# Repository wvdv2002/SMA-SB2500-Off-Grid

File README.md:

# SMA-SB2500-Off-Grid
The grid tie solar inverter SMA Sunny Boy SB2500 is a beautifully designed transformer isolated grid tie inverter. It is probably possible to convert it to an off grid batter inverter by reprogramming or redesigning the logic  board

Checkout my [hackaday.io](https://hackaday.io/project/183357-grid-tie-inverter-sma-sunny-boy-sb2500-openlogic) page for pictures of the inside of the inverter and a project log.

The block diagram from the SB2500 manual.

The inverter has an H-bridge with 4 IGBTs (SKW30NF60) driven by IR2113S mosfet drivers. These drive an 2mH inductor + 4.7uF capacitor step down converter and then a isolation transformer 153V primary/230V secondary 9.6A. On the grid side are three safety relais, EMC filtering and a measurement transformer for the logic board the measure the grid voltages.
All the logic is powered from the DC side, several voltages are generated using a switching power converter which generates all the drive voltages for the IGBT drivers and the logi board.
The logic board contains an SAFC808 microcontroller, probably with an interchangable AT70C020, 2 MBit memory chip, for grid monitoring and sequencing. A DSP56F803 from Freescale provides the switching waveforms. 

The layout is drawn in Kicad. 

Exported kicad images (probably not up to date) are in the images folder. 

The src folder can contain the Freescale DSP code.

The datasheets folder contains datasheets of most of the electronic parts in the inverter.

# Already known
* Switching frequency 16khz
* 250 - 600VDC max input voltage range
* 2200W nominal power
* It is probably challenging to reuse the logic board, as one of the microcontrollers is OTP, maybe it can be bridged and only the DSP used. But then you need a [Freescale USB TAP](https://www.nxp.com/docs/en/user-guide/CWH-UTP-UG.pdf) JTAG programmer to program the DSP. The development environment is not easy to download, but it looks easy to use. 
* The [DEFCON 18 badge](https://media.defcon.org/DEF%20CON%2018/DEF%20CON%2018%20badge/) has used the same development environment and might be a good place to download the development environment and some general guide.

# Already done
* Basic pinout of the logic board connection in Kicad
* Basic layout of the power board important parts in Kicad
* Design new logic board 
* Check if pinout is correct by measuring the voltages on the logic board connector 
* Check all voltage ranges of the voltage measurements on the logic board connector
* Written basic control software
* Light a lightbulb using AC voltage of 100vac at the output of the inverter.

# TODO
* Try to reprogram logic board

# Interesting links
* [Arduino based grid tie inverter repo](https://github.com/MartinStokroos/openMicroInverter)
* [Pic based grid tie inverter repo](https://github.com/rajeshfarswan/UDQ-GRID-1P)
* [STM based grid tie inverter repo](https://github.com/fotherja/Grid_Tie_Inverter)
* [STM based grid tie inverter 2 repo](https://github.com/fotherja/Grid_Tie_Inverter_2)
* [TIVA-C based grid tie inverter](https://github.com/srpoyrek/NIVAS)

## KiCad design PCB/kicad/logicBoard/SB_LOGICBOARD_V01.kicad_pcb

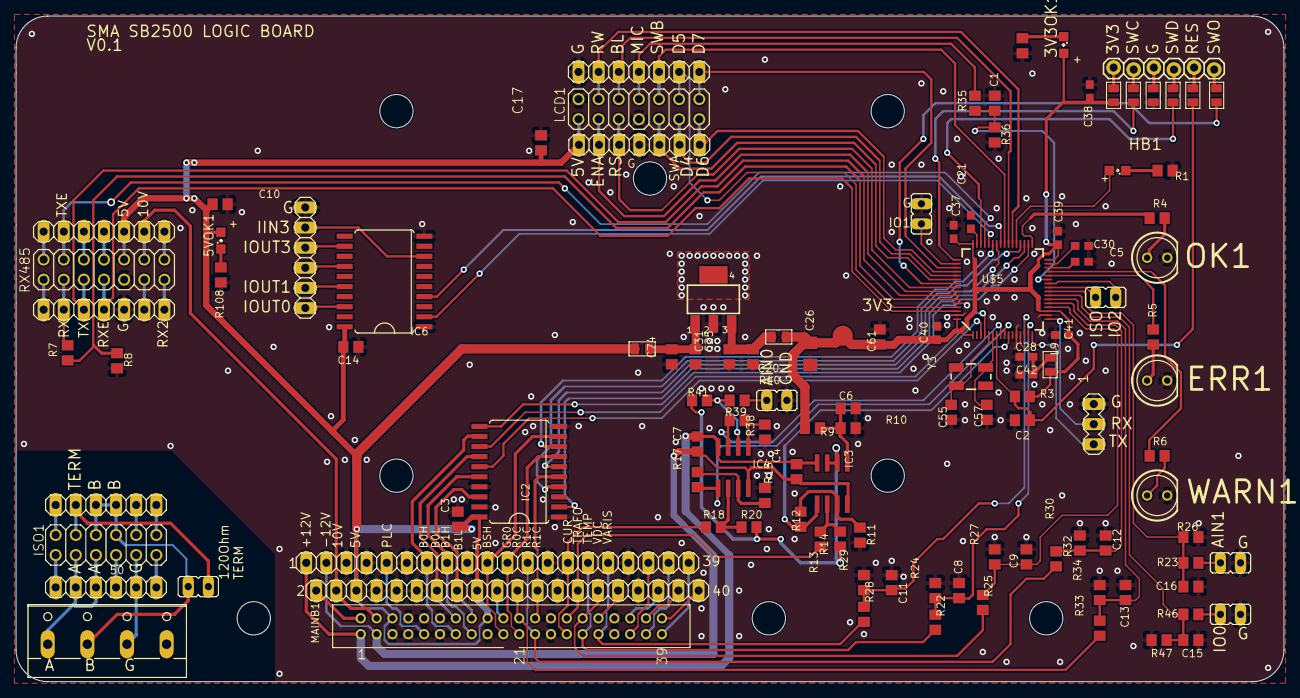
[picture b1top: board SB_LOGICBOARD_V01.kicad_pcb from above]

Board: 2 copper layers, 160.0 x 84.0 mm, 119 parts (0 on the bottom side), 132 nets.

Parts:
3V3: NC; B2,54
3V3OK1, 5VOK1: OSR50805C1E; SML0805
AIN0: JP1E; JP1
C1, C4, C6, C7, C8, C9, C11, C12, C13, C15, C16: 100n/35v; C0805
C2, C3, C10, C14, C17, C20, C25, C31, C61, C74: 100n; C0805
C5: NC; C0603
C21, C28, C30, C37, C38, C39, C40, C41, C42: 2.2uf/6.3v/x7r; C0603
C26: 1206DD106KAT2A; C1206
C55, C57: 22pf; C0805
ERR1: LED5MM
HB1: OSR50805C1E; SML0805
IC1: MCP1826S-3302ED; SOT223
IC2, IC6: 74HCT244DW OR 74VHCT541A; SO20W
IC3, IC4: LM358D; SO08
ISO1: PINHD-2X6; 2X06
J1: ZL201-06G; 1X06_LOCK
JP5, JP6: PINHD-1X20; 1X20
JP7, JP8, JP11, JP12: PINHD-1X7; 1X07
JP9, JP10, JP17: PINHD-1X6; 1X06
JP13, JP15, JP16, JP18, JP19: JP1E; JP1
L1, L2, L3, L6, L7, L8, L9, L26, L27: LCBB-601; L0805
LCD1: PINHD-2X7; 2X07
MAINB1: PINHD-2X20_2MM; 2X20_2MM
OK1: LED5MM
R1, R4, R5, R6: 330; R0805
R3, R12, R14, R17, R20, R39, R41: 10k; R0805
R7, R22, R23, R25, R28, R30, R33, R35, R46: 10K; R0805
R8, R24, R26, R27, R29, R32, R34, R36, R47: 22K; R0805
R9, R10: 22k; R0805
R11, R13: 33k; R0805
R15, R18, R38, R40: 39k; R0805
R108, R109: 2k2/1%; R0805
RX485: PINHD-2X7; 2X07
SV1: MA03-1
U$1: SB_LOGIC_PCB; SB-PCB
U$5: STM32F405RG; TQFP64
WARN1: LED5MM
X1: W237-4
Y3: 8.00M-CFPX104; CRYSTAL-SMD-5X3

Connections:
+3V3: 3V3.TP, 3V3OK1.A, C26.2, C37.1, C38.1, C39.1, C40.1, C41.1, C61.2, L8.1, L9.2, L27.2, R3.2, R9.2, U$5.1, U$5.19, U$5.32, U$5.48, U$5.64
+5V: 5VOK1.A, C3.1, C10.2, C14.1, C17.2, IC2.20, IC6.20, JP6.3, JP6.9, JP8.5, JP11.1, L26.1, LCD1.1, MAINB1.6, MAINB1.18, RX485.10
+12V: C4.1, C7.1, IC3.8, IC4.8, JP5.1, MAINB1.1
-12V: C4.2, C7.2, IC3.4, IC4.4, JP5.2, MAINB1.3
/Microcontroller/IO_IN1: JP19.1, U$5.50
/Microcontroller/IO_IN2: JP18.1, U$5.26
/Microcontroller/ISOLATION_SENSE: JP18.2, U$5.25
/Microcontroller/USART2_RX: SV1.2, U$5.17
/Microcontroller/USART2_TX: SV1.3, U$5.16
/SB_HEADERS/50OHMTOGND: ISO1.7, JP10.4
/SB_HEADERS/120OHMTOA: ISO1.4, JP9.2, JP13.2
/SB_HEADERS/AC_MODEM: JP5.5, MAINB1.9
/SB_HEADERS/ADC_IN0_5V: AIN0.2, R40.1
/SB_HEADERS/ADC_IN1_5V: JP15.2, R23.2
/SB_HEADERS/ADC_UNKNOWN: JP6.16, MAINB1.32
/SB_HEADERS/BRIDGE0_HIN_5V: IC2.12, JP5.7, MAINB1.13
/SB_HEADERS/BRIDGE0_LIN_5V: IC2.14, JP6.7, MAINB1.14
/SB_HEADERS/BRIDGE1_HIN_5V: IC2.16, JP5.8, MAINB1.15
/SB_HEADERS/BRIDGE1_LIN_5V: IC2.18, JP6.8, MAINB1.16
/SB_HEADERS/BRIDGES_SHUTDOWN_5V: IC2.9, JP5.10, MAINB1.19
/SB_HEADERS/CURSENS_5V: JP5.14, MAINB1.27, R18.1
/SB_HEADERS/GRIDRELAY_0_5V: IC2.7, JP5.11, MAINB1.21
/SB_HEADERS/GRIDRELAY_1_5V: IC2.5, JP6.12, MAINB1.24
/SB_HEADERS/IO_IN0_5V: JP16.2, R46.2
/SB_HEADERS/IO_OUT0_5V: IC6.18, JP17.6
/SB_HEADERS/IO_OUT1_5V: IC6.16, JP17.5
/SB_HEADERS/IO_OUT2_5V: IC6.14, JP17.4
/SB_HEADERS/IO_OUT3: IC6.8, JP17.2
/SB_HEADERS/IO_OUT3_5V: IC6.12, JP17.3
/SB_HEADERS/LCD_MIC_5V: JP12.4, LCD1.8, R35.2
/SB_HEADERS/N$25: ISO1.2, JP9.1
/SB_HEADERS/N$29: ISO1.10, JP9.5
/SB_HEADERS/N$30: ISO1.12, JP9.6
/SB_HEADERS/N$31: ISO1.1, JP10.1
/SB_HEADERS/N$42: ISO1.11, JP10.6
/SB_HEADERS/N$53: JP6.10, MAINB1.20
/SB_HEADERS/N$62: JP6.19, MAINB1.38
/SB_HEADERS/N$63: JP6.20, MAINB1.40
/SB_HEADERS/N$86: JP5.18, MAINB1.35
/SB_HEADERS/N$87: JP5.19, MAINB1.37
/SB_HEADERS/N$88: JP5.20, MAINB1.39
/SB_HEADERS/NC1: JP8.3, RX485.6
/SB_HEADERS/NC2: JP8.4, RX485.8
/SB_HEADERS/NC3: JP7.6, RX485.11
/SB_HEADERS/NC4: JP8.7, RX485.14
/SB_HEADERS/NC5: JP8.1, RX485.2
/SB_HEADERS/NC6: JP7.1, RX485.1
/SB_HEADERS/RELAY0_CHECK_5V: JP6.11, MAINB1.22, R33.2
/SB_HEADERS/RELAY1_CHECK_5V: JP5.12, MAINB1.23, R30.2
/SB_HEADERS/RS485_A: ISO1.3, ISO1.5, JP10.2, JP10.3, X1.1
/SB_HEADERS/RS485_B: ISO1.6, ISO1.8, JP9.3, JP9.4, JP13.1, X1.2
/SB_HEADERS/RS485_GND: ISO1.9, JP10.5, X1.3
/SB_HEADERS/RS485_RX_5V: JP7.2, R7.2, RX485.3
/SB_HEADERS/RX2: JP7.7, RX485.13
/SB_HEADERS/SOMESIGNAL: JP6.18, MAINB1.36
/SB_HEADERS/TEMPHEAT_5V: JP5.15, MAINB1.29, R22.2
/SB_HEADERS/TRAFO_5V: JP6.14, MAINB1.28, R13.1
/SB_HEADERS/VARISTOR_SENSE_5V: JP5.16, MAINB1.31, R28.2
/SB_HEADERS/VDCBUS_5V: JP6.15, MAINB1.30, R25.2
/SB_HEADERS/VSUP3: JP6.2, JP8.6, MAINB1.4, RX485.12
ADC_IN0: IC4.7, R39.2, U$5.8
ADC_IN1: C16.1, R23.1, R26.2, U$5.24
BRIDGE0_HIN: IC2.6, U$5.42
BRIDGE0_LIN: IC2.2, U$5.35
BRIDGE1_HIN: IC2.8, U$5.43
BRIDGE1_LIN: IC2.4, U$5.36
BRIDGES_SHUTDOWN: IC2.11, U$5.34
CURSENS: IC4.1, R17.2, U$5.9
GND: AIN0.1, C1.2, C2.1, C3.2, C5.2, C6.2, C8.2, C9.2, C10.1, C11.2, C12.2, C13.2, C14.2, C15.2, C16.2, C17.1, C20.1, C21.1, C25.1, C26.1, C28.2, C30.2, C31.1, C37.2, C38.2, C39.2, C40.2, C41.2, C42.2, C55.2, C57.2, C61.1, C74.2, ERR1.K, IC1.2, IC2.1, IC2.10, IC2.17, IC2.19, IC6.1, IC6.10, JP5.3, JP5.4, JP5.6, JP5.9, JP5.13, JP5.17, JP6.4, JP6.5, JP6.6, JP6.13, JP6.17, JP7.5, JP11.4, JP12.1, JP15.1, JP16.1, JP17.1, JP19.2, L6.1, LCD1.2, LCD1.7, MAINB1.5, MAINB1.7, MAINB1.8, MAINB1.10, MAINB1.11, MAINB1.12, MAINB1.17, MAINB1.25, MAINB1.26, MAINB1.33, MAINB1.34, OK1.K, R1.1, R8.1, R10.1, R11.1, R15.1, R24.1, R26.1, R27.1, R29.1, R32.1, R34.1, R36.1, R38.1, R47.1, R108.1, R109.1, RX485.9, SV1.1, U$5.12, U$5.18, U$5.60, U$5.63, WARN1.K
GRIDRELAY_0: IC2.13, U$5.4
GRIDRELAY_1: IC2.15, U$5.3
HEARTBEAT_LED: HB1.A, U$5.37
IO_IN0: C15.1, R46.1, R47.2, U$5.23
IO_OUT0: IC6.2, U$5.44
IO_OUT1: IC6.4, U$5.41
LCD_BACKL: JP12.3, LCD1.6, U$5.39
LCD_D4: JP11.6, LCD1.11, U$5.53
LCD_D5: JP12.6, LCD1.12, U$5.61
LCD_D6: JP11.7, LCD1.13, U$5.52
LCD_D7: JP12.7, LCD1.14, U$5.51
LCD_ENA: JP11.2, LCD1.3, U$5.57
LCD_MIC: C1.1, R35.1, R36.2, U$5.27
LCD_RS: JP11.3, LCD1.5, U$5.56
LCD_RW: JP12.2, LCD1.4, U$5.38
LCD_SWA: JP11.5, LCD1.9, U$5.54
LCD_SWB: JP12.5, LCD1.10, U$5.40
LED_GREEN: R4.1, U$5.33
LED_RED: R5.1, U$5.28
LED_YELLOW: R6.1, U$5.29
unnamed: 3V3OK1.C, R109.2
unnamed: 5VOK1.C, R108.2
unnamed: C5.1, U$5.30
unnamed: C6.1, IC3.5, R9.1, R10.2
unnamed: C20.2, C25.2, IC1.3, L27.1
unnamed: C21.2, U$5.47
unnamed: C28.1, C42.1, L9.1, U$5.13
unnamed: C30.1, U$5.31
unnamed: C31.2, C74.1, IC1.1, L26.2
unnamed: C55.1, U$5.5, Y3.1
unnamed: C57.1, U$5.6, Y3.3
unnamed: ERR1.A, R5.2
unnamed: HB1.C, R1.2
unnamed: IC3.2, R13.2, R14.1
unnamed: IC3.3, R11.2, R12.1
unnamed: IC4.2, R18.2, R20.1
unnamed: IC4.3, R15.2, R17.1
unnamed: IC4.5, R38.2, R39.1
unnamed: IC4.6, R40.2, R41.1
unnamed: J1.1, L8.2
unnamed: J1.2, L7.2
unnamed: J1.3, L6.2
unnamed: J1.4, L3.2
unnamed: J1.5, L2.2
unnamed: J1.6, L1.2
unnamed: JP6.1, MAINB1.2
unnamed: OK1.A, R4.2
unnamed: R6.2, WARN1.A
RELAY0_CHECK: C13.1, R33.1, R34.2, U$5.22
RELAY1_CHECK: C12.1, R30.1, R32.2, U$5.21
RESET: C2.2, L2.1, R3.1, U$5.7
RS485_RX: R7.1, R8.2, U$5.59
RS485_RXENA: JP7.4, RX485.7, U$5.62
RS485_TX: JP7.3, RX485.5, U$5.58
RS485_TXENA: JP8.2, RX485.4, U$5.45
SWCLK: L7.1, U$5.49
SWDIO: L3.1, U$5.46
SWO: L1.1, U$5.55
TEMPHEAT: C8.1, R22.1, R24.2, U$5.15
TRAFO: IC3.1, R12.2, U$5.10
VARISTOR_SENSE: C11.1, R28.1, R29.2, U$5.14
VCC/2: IC3.6, IC3.7, R14.2, R20.2, R41.2
VDCBUS: C9.1, R25.1, R27.2, U$5.20

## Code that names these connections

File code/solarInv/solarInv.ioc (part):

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Mcu.Name=STM32F405RGTx
Mcu.Package=LQFP64
Mcu.UserName=STM32F405RGTx
PA0-WKUP.Signal=ADCx_IN0
PA1.GPIOParameters=GPIO_Label
PA1.GPIO_Label=TEMPHEAT
PA1.Signal=ADCx_IN1
PA10.GPIOParameters=GPIO_Speed,GPIO_Label
PA10.GPIO_Label=BRIDGE1_HIN
PA10.GPIO_Speed=GPIO_SPEED_FREQ_HIGH
PA10.Signal=S_TIM1_CH3
PA11.GPIOParameters=GPIO_Label
PA11.GPIO_Label=IO_OUT0
PA11.Signal=GPIO_Output
PA12.GPIOParameters=GPIO_Label
PA12.GPIO_Label=RS485_TXENA
PA12.Signal=GPIO_Output
PA13.Mode=Trace_Asynchronous_SW
PA13.Signal=SYS_JTMS-SWDIO
PA14.Mode=Trace_Asynchronous_SW
PA14.Signal=SYS_JTCK-SWCLK
PA15.GPIOParameters=GPIO_PuPd,GPIO_Label
PA15.GPIO_Label=IO_IN1
PA15.GPIO_PuPd=GPIO_NOPULL
PA15.Signal=GPIO_Input
PA2.GPIOParameters=GPIO_Speed,GPIO_Label
PA2.GPIO_Label=USART2_TX
PA2.GPIO_Speed=GPIO_SPEED_FREQ_HIGH
PA2.Mode=Asynchronous
PA2.Signal=USART2_TX
PA3.GPIOParameters=GPIO_Speed,GPIO_Label
PA3.GPIO_Label=USART2_RX
PA3.GPIO_Speed=GPIO_SPEED_FREQ_HIGH
PA3.Mode=Asynchronous
PA3.Signal=USART2_RX
PA4.GPIOParameters=GPIO_Label
PA4.GPIO_Label=VDCBUS
PA4.Signal=ADCx_IN4
PA5.GPIOParameters=GPIO_Label
PA5.GPIO_Label=RELAY_CHECK1
PA5.Signal=ADCx_IN5
PA6.GPIOParameters=GPIO_Label
PA6.GPIO_Label=RELAY_CHECK0
PA6.Signal=ADCx_IN6
PA7.GPIOParameters=GPIO_Label
PA7.GPIO_Label=IO_IN0
PA7.Signal=ADCx_IN7
PA8.GPIOParameters=GPIO_Label
PA8.GPIO_Label=IO_OUT1
PA8.Signal=GPIO_Output
PA9.GPIOParameters=GPIO_Speed,GPIO_Label
PA9.GPIO_Label=BRIDGE0_HIN
PA9.GPIO_Speed=GPIO_SPEED_FREQ_HIGH
PA9.Signal=S_TIM1_CH2
PB0.GPIOParameters=GPIO_Label
PB0.GPIO_Label=IO_IN2
PB0.Signal=ADCx_IN8
PB1.GPIOParameters=GPIO_Label
PB1.GPIO_Label=LCD_MIC
PB1.Signal=ADCx_IN9
PB10.GPIOParameters=GPIO_Label
PB10.GPIO_Label=LED_YELLOW
PB10.Signal=GPIO_Output
PB11.GPIOParameters=GPIO_PuPd,GPIO_Label,GPIO_Mode
PB11.GPIO_Label=DONOTUSECOMPATIBILITY
PB11.GPIO_Mode=GPIO_MODE_INPUT
PB11.GPIO_PuPd=GPIO_NOPULL
PB11.Signal=GPIO_Input
PB12.GPIOParameters=GPIO_Label
PB12.GPIO_Label=LED_GREEN
PB12.Signal=GPIO_Output
PB13.GPIOParameters=GPIO_Speed,PinState,GPIO_Label
PB13.GPIO_Label=BRIDGES_SHUTDOWN
PB13.GPIO_Speed=GPIO_SPEED_FREQ_MEDIUM
PB13.PinState=GPIO_PIN_SET
PB13.Signal=GPIO_Output
PB14.GPIOParameters=GPIO_ModeDefaultPP,GPIO_Speed,GPIO_PuPd,GPIO_Label
PB14.GPIO_Label=BRIDGE0_LIN
PB14.GPIO_ModeDefaultPP=GPIO_MODE_AF_PP
PB14.GPIO_PuPd=GPIO_NOPULL
PB14.GPIO_Speed=GPIO_SPEED_FREQ_HIGH
PB14.Mode=PWM Generation2 CH2 CH2N
PB14.Signal=TIM1_CH2N
PB15.GPIOParameters=GPIO_ModeDefaultPP,GPIO_Speed,GPIO_PuPd,GPIO_Label
PB15.GPIO_Label=BRIDGE1_LIN
PB15.GPIO_ModeDefaultPP=GPIO_MODE_AF_PP
PB15.GPIO_PuPd=GPIO_NOPULL
PB15.GPIO_Speed=GPIO_SPEED_FREQ_HIGH
PB15.Mode=PWM Generation3 CH3 CH3N
PB15.Signal=TIM1_CH3N
PB2.GPIOParameters=GPIO_Label
PB2.GPIO_Label=LED_RED
PB2.Signal=GPIO_Output
PB3.Mode=Trace_Asynchronous_SW
PB3.Signal=SYS_JTDO-SWO
PB4.GPIOParameters=GPIO_Label
PB4.GPIO_Label=LCD_RS
PB4.Signal=GPIO_Output
PB5.GPIOParameters=GPIO_Speed,PinState,GPIO_PuPd,GPIO_Label,GPIO_ModeDefaultOutputPP
PB5.GPIO_Label=LCD_ENA
PB5.GPIO_ModeDefaultOutputPP=GPIO_MODE_OUTPUT_PP
PB5.GPIO_PuPd=GPIO_NOPULL
PB5.GPIO_Speed=GPIO_SPEED_FREQ_LOW
PB5.PinState=GPIO_PIN_RESET
PB5.Signal=GPIO_Output
PB6.GPIOParameters=GPIO_Speed,GPIO_Label
PB6.GPIO_Label=RS485_TX
PB6.GPIO_Speed=GPIO_SPEED_FREQ_HIGH
PB6.Mode=Asynchronous
PB6.Signal=USART1_TX
PB7.GPIOParameters=GPIO_Speed,GPIO_Label
PB7.GPIO_Label=RS485_RX
PB7.GPIO_Speed=GPIO_SPEED_FREQ_HIGH
PB7.Mode=Asynchronous
PB7.Signal=USART1_RX
PB8.GPIOParameters=GPIO_Label
PB8.GPIO_Label=LCD_D5
PB8.Signal=GPIO_Output
PB9.GPIOParameters=GPIO_Label
PB9.GPIO_Label=RS485_RXENA
PB9.Signal=GPIO_Output
PC0.GPIOParameters=GPIO_Label
PC0.GPIO_Label=ADC_IN0
PC0.Signal=ADCx_IN10
PC1.GPIOParameters=GPIO_PuPd,GPIO_Label,GPIO_Mode
PC1.GPIO_Label=CURSENS
PC1.GPIO_Mode=GPIO_MODE_ANALOG
PC1.GPIO_PuPd=GPIO_NOPULL
PC1.Signal=ADCx_IN11
PC10.GPIOParameters=GPIO_Label
PC10.GPIO_Label=LCD_D7
PC10.Signal=GPIO_Output
PC11.GPIOParameters=GPIO_Label
PC11.GPIO_Label=LCD_D6
PC11.Signal=GPIO_Output
PC12.GPIOParameters=GPIO_Label
PC12.GPIO_Label=LCD_D4
PC12.Signal=GPIO_Output
PC14-OSC32_IN.GPIOParameters=GPIO_Label
PC14-OSC32_IN.GPIO_Label=GRIDRELAY_1
PC14-OSC32_IN.Signal=GPIO_Output
PC15-OSC32_OUT.GPIOParameters=GPIO_Label
PC15-OSC32_OUT.GPIO_Label=GRIDRELAY_0
PC15-OSC32_OUT.Signal=GPIO_Output
PC2.GPIOParameters=GPIO_PuPd,GPIO_Label,GPIO_Mode
PC2.GPIO_Label=TRAFO
PC2.GPIO_Mode=GPIO_MODE_ANALOG
PC2.GPIO_PuPd=GPIO_NOPULL
PC2.Signal=ADCx_IN12
PC4.GPIOParameters=GPIO_Label
PC4.GPIO_Label=ADC_IN1
PC4.Signal=ADCx_IN14
PC5.GPIOParameters=GPIO_Label
PC5.GPIO_Label=ISOLATION_SENSE
PC5.Signal=ADCx_IN15
PC6.GPIOParameters=GPIO_Label
PC6.GPIO_Label=LED_HEARTBEAT
PC6.Signal=GPIO_Output
PC7.GPIOParameters=GPIO_Label
PC7.GPIO_Label=LCD_RW
PC7.Signal=GPIO_Output
PC8.GPIOParameters=GPIO_Label
PC8.GPIO_Label=LCD_BACKL
PC8.Signal=GPIO_Output
PC9.GPIOParameters=GPIO_PuPd,GPIO_Label
PC9.GPIO_Label=LCD_SWB
PC9.GPIO_PuPd=GPIO_PULLUP
PC9.Signal=GPIO_Input
PD2.GPIOParameters=GPIO_PuPd,GPIO_Label
PD2.GPIO_Label=LCD_SWA
PD2.GPIO_PuPd=GPIO_PULLUP
PD2.Signal=GPIO_Input
RCC.HSE_VALUE=8000000
RCC.SYSCLKFreq_VALUE=168000000
RCC.SYSCLKSource=RCC_SYSCLKSOURCE_PLLCLK
board=solarInv

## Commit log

2022-01-02 Added PCB design, datasheets and images, first real commit
2022-01-02 Moved checkout link higher and caption for the block diagram
2022-01-02 Added some pictures of the pcbs
2022-01-16 Added daughterboards from logic board pinout and voltages. Added logicboard size sketches and a few pictures.
2022-07-27 reorganised datasheets
2022-07-27 Moved PCB files
2022-07-27 Added some more pictures
2022-08-22 Updated gitignore for C files
2022-08-22 Updated some pins and voltages
2022-08-22 Removed build directories
2022-08-22 Added STM32F4 control code
2022-08-22 Added some logic board parts
2022-08-22 Added gitignore for LTSpice simulations
2022-08-22 First LTSpice simulation
2022-08-22 Updated simulation
2022-08-22 Logic board PCB design added (converterd from Eagle) and moved powerboard schematic drawings to other folder
2022-08-22 Added logicboard pcb and schematic
2022-08-30 Updated the kicad logicboard
2022-08-30 Added extra timer for sinusoid generation, PWM pin settings now correct, led control improved
2022-08-30 Fixed link in readme
2022-08-30 Added front and back PCB render
2022-08-30 Added code for the old original SMA PCB
2022-09-05 Doubled sinus timer speed, Enabled RS485 only reception for now, enabled float printf
2022-09-05 Vbus safety checks, slowly rising Vout, deadtime control from setpoint
2022-09-05 Updated readme with what is done
2022-09-05 Added screenshot and controller image
